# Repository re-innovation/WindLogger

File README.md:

# Low Cost Data Logger for Wind Speed Parameters
This repository has the open-source files for a Data Logger for Wind Speed and other small wind turbine parameters.

So far there have been two different versions of this unit:
* Version 1 was released in 2014. This was basic add on shield for the 'DataDuino' (an Arduino based SD card datalogger from www.re-innovation.co.uk)
* Version 2 was released on 2016. This was a surface mount design with additional functions such as solar PV charging.

The Wind Logger was originally designed by Matt Little of www.re-innovation.co.uk
Contact: info@re-innovation.co.uk

Please see: www.re-innovation.co.uk and search for 'wind datalogger' for more details.
Some more details are available here:
https://www.re-innovation.co.uk/docs/wind-datalogger/

The folders in this repository include:
	
* WindLogger_PCB
The PCB files were created in KiCAD PCB design software
These are in Windlogger_PCB
There are the KICAD project files and the GERBER files for both the DataDuino and the Windlogger Shield	

* WindLogger_FIRMWARE
Example code has been written for uploading via the Arduino IDE.

* WindLogger_FIXINGS
The CAD design for fixing system for an anemometer and a wind vane.
These is a work in progress. Originally draw using CorelDraw - I hope to update/convert this soon.
	
* WindLogger_INSTRUCTIONS
These are the instructions in a number of formats and languages.

## Version 1 - 2014
Overview of the design:
  A PCF8563 Real Time Clock is used to timestamp the data.

  Pin D3 is set up to cound pulses from a sensor (such as a anemometer or flow sensor)
 
  Pins D7,D8,D9 are set up to record digital information (0 or 1)
  
  Pins A0 to A3 are set up to record analogue information (0 to 1024)
  
  Each logger has a reference (user adjustable from 00-99).
  
  Data is written to a .csv file created on an SD card.
  
  A new file is created each day. If file alreay present then data is appended.
  
  The file name is created from the reference number and the date in the format:
  
  RXXDXXXX.csv, where RXX is the reference number and DXXXX is the date in the format DDMM. 
  
  Data is stored with human readable headers. Check the Arduino code for these.
  
  You can adjust the parameters of the device using serial commands. These parameters are stored in EEPROM.
  These are:
  * R??E - This will change the reference number to ??
  * T??????E - This will change the time to HHMMSS
  * D??????E - This will change the date to DDMMYY
  * S?????E - This will change the sample period to ????? seconds. Set to 00001 for 1 second data, set to 03600 for 1 hour data. (The minimum is 1 second data. The maximum is 99999 seconds)

## Version 3 - 2016
 
This newer version mainly covers a new circuit board which was designed as a surface mount design. The Code on this board has additional changes, but not too different functionality.

## Version 4 - 2020

This is work in progress. I'm trying to create a better PCB design which will also have WiFi and GPRS/2G connectivity for your data.

The wind speed logging unit is a plug in board onto a data-logging main unit.

##  Data Processing
These are programs to take the data on the SD card and produce nice graphs with it.
This is a work in progress.
https://github.com/re-innovation/CSVviewer

## Changes to do!

* PCF8563 - not accurate enough. Use DS3231 with temperature compensation.
* Add data upload via WiFi
* Add data upload via GPRS

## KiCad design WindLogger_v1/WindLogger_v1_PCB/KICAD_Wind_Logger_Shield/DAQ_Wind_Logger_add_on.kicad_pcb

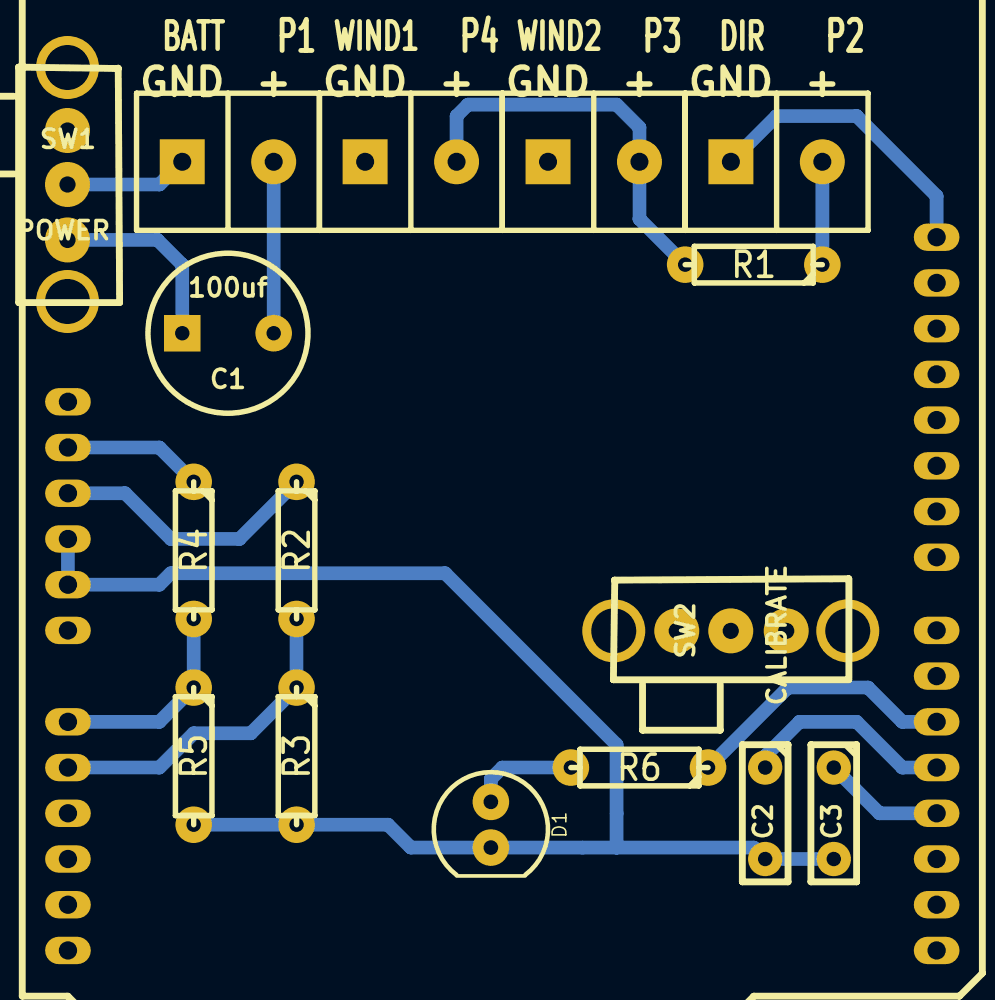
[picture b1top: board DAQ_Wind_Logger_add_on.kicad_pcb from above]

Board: 2 copper layers, 17 parts (0 on the bottom side), 12 nets.

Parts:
C1: 100uf; C2V8_large_pad
C2, C3: C; C1_wide_lg_pad_2
D1: DATA; LED-5MM_larg_pad
P1: BATT; SIL-2_screw_terminal
P2: DIR; SIL-2_screw_terminal
P3: WIND2; SIL-2_screw_terminal
P4: WIND1; SIL-2_screw_terminal
R1: 10k; R3-LARGE_PADS_0_8_hole
R2, R3, R4: 47k; R3-LARGE_PADS_0_8_hole
R5: Therm 47k; R3-LARGE_PADS_0_8_hole
R6: 1k; R3-LARGE_PADS_0_8_hole
SHIELD1: ARDUINO_SHIELD; ARDUINO_SHIELD_040pins_no_hole
SW1: POWER; SW_SPDT_rapid_760271
SW2: CALIBRATE; SW_SPDT_rapid_760271

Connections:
+BATT: C1.1, R2.1, SHIELD1.5V, SW1.1
GND: C2.2, C3.2, D1.2, P3.2, P4.2, R1.2, R3.2, R5.2, SHIELD1.GND1, SHIELD1.GND2, SW2.2
unnamed: P1.1, SW1.2
unnamed: SHIELD1.7, SW2.1
unnamed: P2.2, R1.1, SHIELD1.AD2
unnamed: C1.2, P1.2, R2.2, R3.1, SHIELD1.AD1
unnamed: R4.2, R5.1, SHIELD1.AD0
unnamed: P2.1, R4.1, SHIELD1.3V3, SHIELD1.AREF
unnamed: D1.1, R6.2
unnamed: R6.1, SHIELD1.5
unnamed: C2.1, P3.1, SHIELD1.4
unnamed: C3.1, P4.1, SHIELD1.3

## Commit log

2014-05-20 Changed readme
2014-08-15 Update 15/8/14
    New Arduino code. Updated PCB. Updated Instructions
2014-08-15 Arduino code update
2014-10-29 Update with Instructions
    Put in different language instructions
2014-10-29 Updated Instructions
2020-11-21 Large update and rearrange of windlogger files
    Added both version 1 and version 3.
2020-11-21 Change readme to markdown
